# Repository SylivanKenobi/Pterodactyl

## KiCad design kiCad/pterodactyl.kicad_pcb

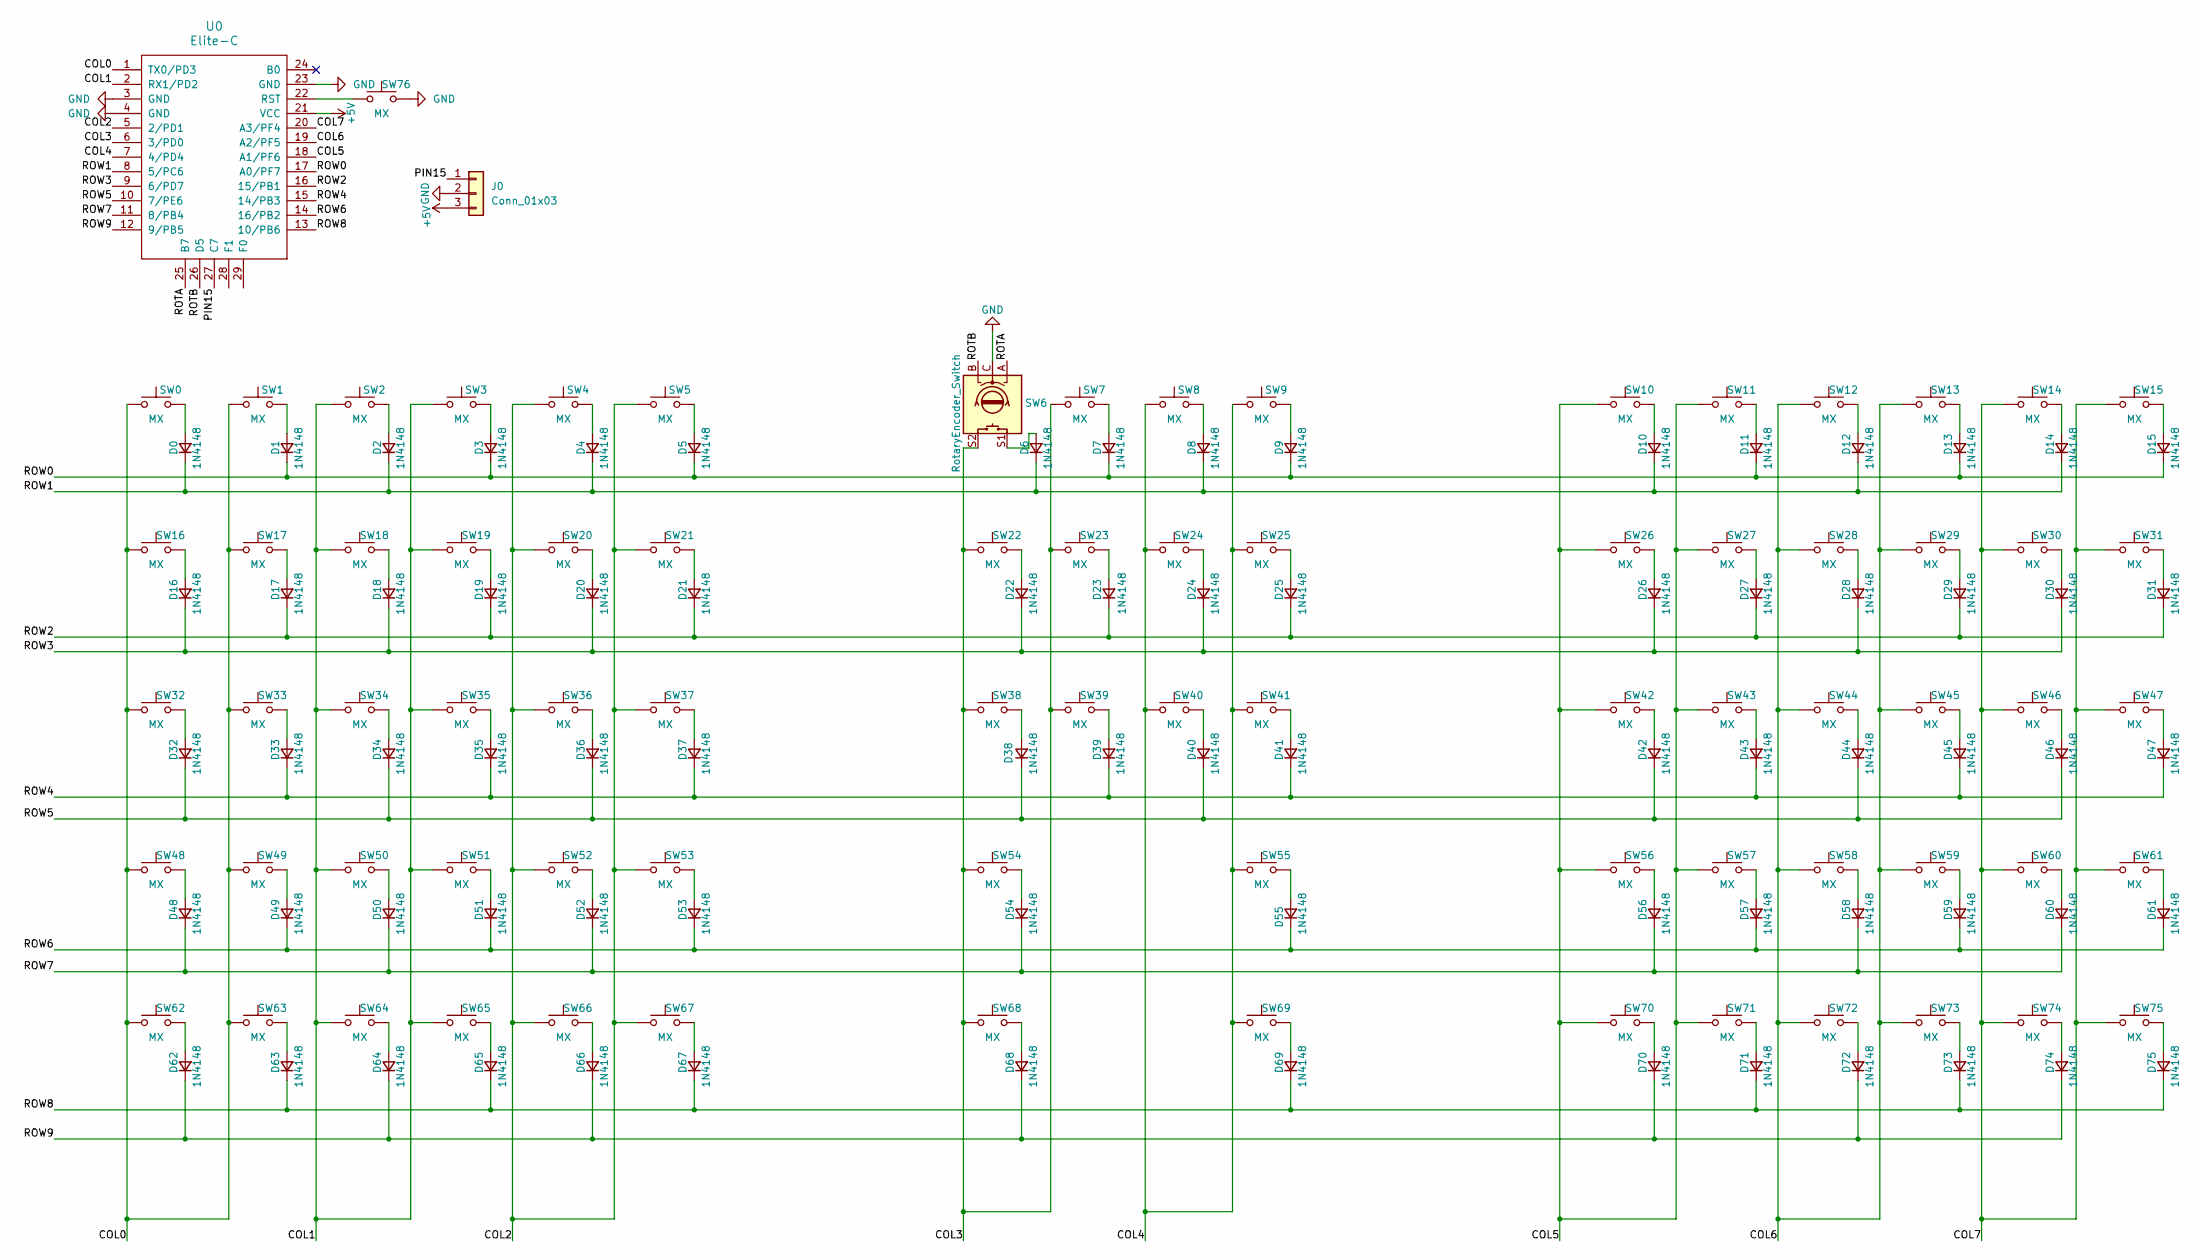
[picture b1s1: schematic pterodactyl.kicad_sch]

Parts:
D0, D1, D2, D3, D4, D5, D6, D7, D8, D9, D10, D11, D12, D13, D14, D15, D16, D17, D18, D19, D20, D21, D22, D23, D24, D25, D26, D27, D28, D29, D30, D31, D32, D33, D34, D35, D36, D37, D38, D39, D40, D41, D42, D43, D44, D45, D46, D47, D48, D49, D50, D51, D52, D53, D54, D55, D56, D57, D58, D59, D60, D61, D62, D63, D64, D65, D66, D67, D68, D69, D70, D71, D72, D73, D74, D75: 1N4148; D_DO-35_SOD27_P7.62mm_Horizontal
J0: Conn_01x03; PinHeader_1x03_P2.54mm_Vertical
SW0, SW1, SW2, SW3, SW4, SW5, SW7, SW8, SW9, SW10, SW11, SW12, SW13, SW14, SW15, SW16, SW17, SW18, SW19, SW20, SW21, SW22, SW23, SW24, SW25, SW26, SW27, SW28, SW29, SW30, SW31, SW32, SW33, SW34, SW35, SW36, SW37, SW38, SW39, SW40, SW41, SW42, SW43, SW44, SW45, SW46, SW47, SW48, SW49, SW50, SW51, SW52, SW53, SW54, SW55, SW56, SW57, SW58, SW59, SW60, SW61, SW62, SW63, SW64, SW65, SW66, SW67, SW68, SW69, SW70, SW71, SW72, SW73, SW74, SW75: MX; Kailh_socket_MX
SW6: RotaryEncoder_Switch; RotaryEncoder_EC11
SW76: MX; PushButton_6x6mm_TH_Pretty
U0: Elite-C

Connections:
+5V: J0.3, U0.21 (VCC)
/COL0: SW0.1, SW1.1, SW16.1, SW17.1, SW32.1, SW33.1, SW48.1, SW49.1, SW62.1, SW63.1, U0.1 (TX0/PD3)
/COL1: SW2.1, SW3.1, SW18.1, SW19.1, SW34.1, SW35.1, SW50.1, SW51.1, SW64.1, SW65.1, U0.2 (RX1/PD2)
/COL2: SW4.1, SW5.1, SW20.1, SW21.1, SW36.1, SW37.1, SW52.1, SW53.1, SW66.1, SW67.1, U0.5 (2/PD1)
/COL3: SW6.S2, SW7.1, SW22.1, SW23.1, SW38.1, SW39.1, SW54.1, SW68.1, U0.6 (3/PD0)
/COL4: SW8.1, SW9.1, SW24.1, SW25.1, SW40.1, SW41.1, SW55.1, SW69.1, U0.7 (4/PD4)
/COL5: SW10.1, SW11.1, SW26.1, SW27.1, SW42.1, SW43.1, SW56.1, SW57.1, SW70.1, SW71.1, U0.18 (A1/PF6)
/COL6: SW12.1, SW13.1, SW28.1, SW29.1, SW44.1, SW45.1, SW58.1, SW59.1, SW72.1, SW73.1, U0.19 (A2/PF5)
/COL7: SW14.1, SW15.1, SW30.1, SW31.1, SW46.1, SW47.1, SW60.1, SW61.1, SW74.1, SW75.1, U0.20 (A3/PF4)
/PIN15: J0.1, U0.27 (C7)
/ROTA: SW6.A, U0.25 (B7)
/ROTB: SW6.B, U0.26 (D5)
/ROW0: D1.1 (K), D3.1 (K), D5.1 (K), D7.1 (K), D9.1 (K), D11.1 (K), D13.1 (K), D15.1 (K), U0.17 (A0/PF7)
/ROW1: D0.1 (K), D2.1 (K), D4.1 (K), D6.1 (K), D8.1 (K), D10.1 (K), D12.1 (K), D14.1 (K), U0.8 (5/PC6)
/ROW2: D17.1 (K), D19.1 (K), D21.1 (K), D23.1 (K), D25.1 (K), D27.1 (K), D29.1 (K), D31.1 (K), U0.16 (15/PB1)
/ROW3: D16.1 (K), D18.1 (K), D20.1 (K), D22.1 (K), D24.1 (K), D26.1 (K), D28.1 (K), D30.1 (K), U0.9 (6/PD7)
/ROW4: D33.1 (K), D35.1 (K), D37.1 (K), D39.1 (K), D41.1 (K), D43.1 (K), D45.1 (K), D47.1 (K), U0.15 (14/PB3)
/ROW5: D32.1 (K), D34.1 (K), D36.1 (K), D38.1 (K), D40.1 (K), D42.1 (K), D44.1 (K), D46.1 (K), U0.10 (7/PE6)
/ROW6: D49.1 (K), D51.1 (K), D53.1 (K), D55.1 (K), D57.1 (K), D59.1 (K), D61.1 (K), U0.14 (16/PB2)
/ROW7: D48.1 (K), D50.1 (K), D52.1 (K), D54.1 (K), D56.1 (K), D58.1 (K), D60.1 (K), U0.11 (8/PB4)
/ROW8: D63.1 (K), D65.1 (K), D67.1 (K), D69.1 (K), D71.1 (K), D73.1 (K), D75.1 (K), U0.13 (10/PB6)
/ROW9: D62.1 (K), D64.1 (K), D66.1 (K), D68.1 (K), D70.1 (K), D72.1 (K), D74.1 (K), U0.12 (9/PB5)
GND: J0.2, SW6.C, SW76.2, U0.3 (GND), U0.4 (GND), U0.23 (GND)
unnamed: D0.2 (A), SW0.2
unnamed: D1.2 (A), SW1.2
unnamed: D2.2 (A), SW2.2
unnamed: D3.2 (A), SW3.2
unnamed: D4.2 (A), SW4.2
unnamed: D5.2 (A), SW5.2
unnamed: D6.2 (A), SW6.S1
unnamed: D7.2 (A), SW7.2
unnamed: D8.2 (A), SW8.2
unnamed: D9.2 (A), SW9.2
unnamed: D10.2 (A), SW10.2
unnamed: D11.2 (A), SW11.2
unnamed: D12.2 (A), SW12.2
unnamed: D13.2 (A), SW13.2
unnamed: D14.2 (A), SW14.2
unnamed: D15.2 (A), SW15.2
unnamed: D16.2 (A), SW16.2
unnamed: D17.2 (A), SW17.2
unnamed: D18.2 (A), SW18.2
unnamed: D19.2 (A), SW19.2
unnamed: D20.2 (A), SW20.2
unnamed: D21.2 (A), SW21.2
unnamed: D22.2 (A), SW22.2
unnamed: D23.2 (A), SW23.2
unnamed: D24.2 (A), SW24.2
unnamed: D25.2 (A), SW25.2
unnamed: D26.2 (A), SW26.2
unnamed: D27.2 (A), SW27.2
unnamed: D28.2 (A), SW28.2
unnamed: D29.2 (A), SW29.2
unnamed: D30.2 (A), SW30.2
unnamed: D31.2 (A), SW31.2
unnamed: D32.2 (A), SW32.2
unnamed: D33.2 (A), SW33.2
unnamed: D34.2 (A), SW34.2
unnamed: D35.2 (A), SW35.2
unnamed: D36.2 (A), SW36.2
unnamed: D37.2 (A), SW37.2
unnamed: D38.2 (A), SW38.2
unnamed: D39.2 (A), SW39.2
unnamed: D40.2 (A), SW40.2
unnamed: D41.2 (A), SW41.2
unnamed: D42.2 (A), SW42.2
unnamed: D43.2 (A), SW43.2
unnamed: D44.2 (A), SW44.2
unnamed: D45.2 (A), SW45.2
unnamed: D46.2 (A), SW46.2
unnamed: D47.2 (A), SW47.2
unnamed: D48.2 (A), SW48.2
unnamed: D49.2 (A), SW49.2
unnamed: D50.2 (A), SW50.2
unnamed: D51.2 (A), SW51.2
unnamed: D52.2 (A), SW52.2
unnamed: D53.2 (A), SW53.2
unnamed: D54.2 (A), SW54.2
unnamed: D55.2 (A), SW55.2
unnamed: D56.2 (A), SW56.2
unnamed: D57.2 (A), SW57.2
unnamed: D58.2 (A), SW58.2
unnamed: D59.2 (A), SW59.2
unnamed: D60.2 (A), SW60.2
unnamed: D61.2 (A), SW61.2
unnamed: D62.2 (A), SW62.2
unnamed: D63.2 (A), SW63.2
unnamed: D64.2 (A), SW64.2
unnamed: D65.2 (A), SW65.2
unnamed: D66.2 (A), SW66.2
unnamed: D67.2 (A), SW67.2
unnamed: D68.2 (A), SW68.2
unnamed: D69.2 (A), SW69.2
unnamed: D70.2 (A), SW70.2
unnamed: D71.2 (A), SW71.2
unnamed: D72.2 (A), SW72.2
unnamed: D73.2 (A), SW73.2
unnamed: D74.2 (A), SW74.2
unnamed: D75.2 (A), SW75.2
unnamed: SW76.1, U0.22 (RST)

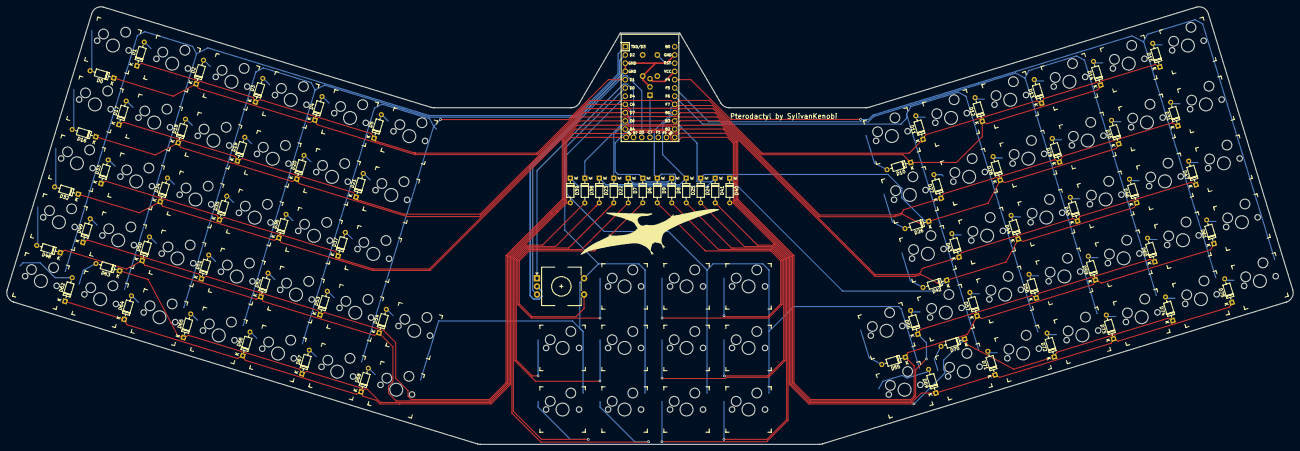
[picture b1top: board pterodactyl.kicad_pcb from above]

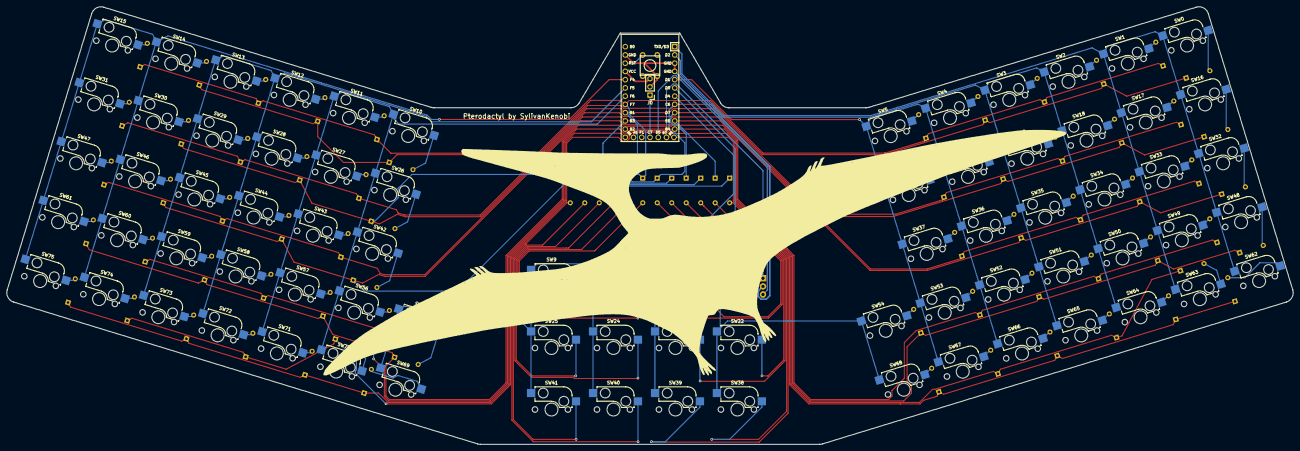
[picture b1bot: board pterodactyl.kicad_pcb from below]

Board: 2 copper layers, 396.4 x 134.8 mm, 155 parts (2 on the bottom side), 100 nets.

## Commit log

2024-05-03 start pterodactyl keyboard
2024-05-11 finish routing
2024-05-12 add edge cuts, flip controller
2024-10-24 rewire everything, change ergonomics
2024-10-25 fix annotations, start routing
2024-10-26 add most of routing
2024-10-27 finish routing, add edge cuts, add artwork
2024-10-28 add mounting points, cleanup some footprints
2024-11-16 add case stls
